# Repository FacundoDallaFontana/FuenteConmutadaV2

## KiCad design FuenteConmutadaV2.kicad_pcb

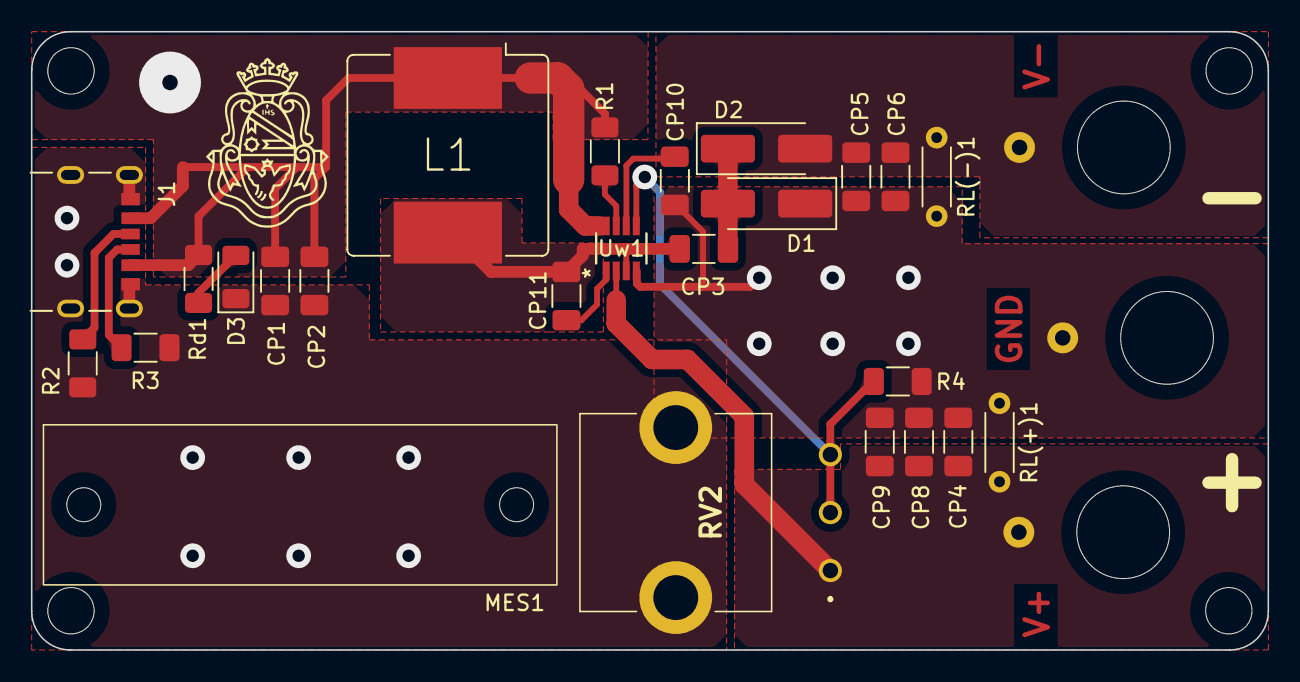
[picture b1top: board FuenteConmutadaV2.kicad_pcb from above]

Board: 2 copper layers, 80.0 x 40.0 mm, 29 parts (1 on the bottom side), 13 nets.

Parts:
CP1, CP2, CP4, CP5, CP6, CP8, CP9: 22uF; C_1206_3216Metric_Pad1.33x1.80mm_HandSolder
CP3: 1uF; C_1206_3216Metric_Pad1.33x1.80mm_HandSolder
CP10: 4.7uF; C_1206_3216Metric_Pad1.33x1.80mm_HandSolder
CP11: 0.1uF; C_1206_3216Metric_Pad1.33x1.80mm_HandSolder
D1, D2: D_Schottky; D_SMA_Handsoldering
D3: LED Red; LED_1206_3216Metric
J1: USB_C_Receptacle_USB2.0; AMPHENOL_10164359-00011LF
J2, J3, J4: Conn_01x01_Pin; Banana_CT_6mm
L1: 10uH; L_Bourns_SRR1208_12.7x12.7mm
MES1: Voltmeter_DC; PRT-14313
R1: 30k; R_1206_3216Metric_Pad1.30x1.75mm_HandSolder
R2, R3, R4: 5k; R_1206_3216Metric_Pad1.30x1.75mm_HandSolder
RL(+)1: 470; R_Axial_DIN0204_L3.6mm_D1.6mm_P5.08mm_Horizontal
RL(-)1: 470; R_Axial_DIN0204_L3.6mm_D1.6mm_P5.08mm_Horizontal
RV2: R_Potentiometer_MountingPin; PDB12M4251105BF
Rd1: 220; R_1206_3216Metric_Pad1.30x1.75mm_HandSolder
TCdE FCEFYN: Logo
Uw1: MP3437GJ-P; TSOT23-8_MP3437_MNP-M

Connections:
+5V: CP1.2, CP2.2, J1.A9 (VBUS), J1.B9 (VBUS), L1.1, R1.1, Rd1.1, Uw1.8 (VIN)
/SW: CP3.1, CP11.2, L1.2, Uw1.3 (SW)
/Vo+: CP4.2, CP8.2, CP9.2, J2.1, RL(+)1.2, RV2.1, Uw1.2 (VOUT)
/Vo-: CP5.2, CP6.2, D2.2 (A), J4.1, RL(-)1.1
GND: CP1.1, CP2.1, CP4.1, CP5.1, CP6.1, CP8.1, CP9.1, CP10.2, D1.1 (K), D3.1 (K), J1.A12 (GND), J1.B12 (GND), J1.S1 (SHIELD), J3.1, R2.2, R3.2, R4.2, RL(+)1.1, RL(-)1.2, RV2.MP (MountPin), Uw1.4 (GND)
unnamed: CP3.2, D1.2 (A), D2.1 (K)
unnamed: D3.2 (A), Rd1.2
unnamed: J1.A5 (CC1), R2.1
unnamed: J1.B5 (CC2), R3.1
unnamed: CP11.1, Uw1.1 (BST)
unnamed: R1.2, Uw1.7 (EN)
unnamed: R4.1, RV2.2, RV2.3, Uw1.5 (FB)
unnamed: CP10.1, Uw1.6 (VDD)

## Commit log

2024-08-15 Actualizacion Kicad 8.0
2024-08-15 cambios
2024-08-16 LED indicador y Resistencias de carga
    Se agrego un LED rojo indicador de que se encuentra alimentada la placa, junto a resistencias con agujeros pasantes para las cargas.
2024-08-17 Led-Huecos voltimetro y esquinas -R paralelo
    -Cambie huella de LED a 1206 y posicione junto al display.
    -Agregue agujeros (3mm) para fijar el voltímetro .
    - Agregue R paralelo al potenciómetro.
    -cambie Huecos de las esquinas a 3mm y un margen de 5 mm (Diametro)
2024-08-21 Cambios+pad banana
    Pad banana diseñado
    ajuste te tamaño de placa 80x40mm
    ajuste vias
    +mounting holes
2024-08-21 +pad 5V
2024-08-21 Cambios
    +pote
    +conectores banana
    +usb_c
    +pads, footprints & 3dmodels
2024-08-22 Correccion footprint banana
2024-08-22 Correccion footprint banana V2
    Conexion completa del pad inferior a GND.
2024-08-22 Optimización
2024-08-22 Logos
    Agregue logos en las capas de serigrafía
2024-08-23 +Versiones con pads para Voltimetro (V2.1&V2.2)
    No se hicieron modificaciones en el PCB original, solo se agregaron 2 archivos de PCB nuevos.
    Tambien se agrego una V2 del footprint del Voltimetro un poco mas acertada al tamaño fisico de este.(se puede observar en los nuevos archivos de PCB)
